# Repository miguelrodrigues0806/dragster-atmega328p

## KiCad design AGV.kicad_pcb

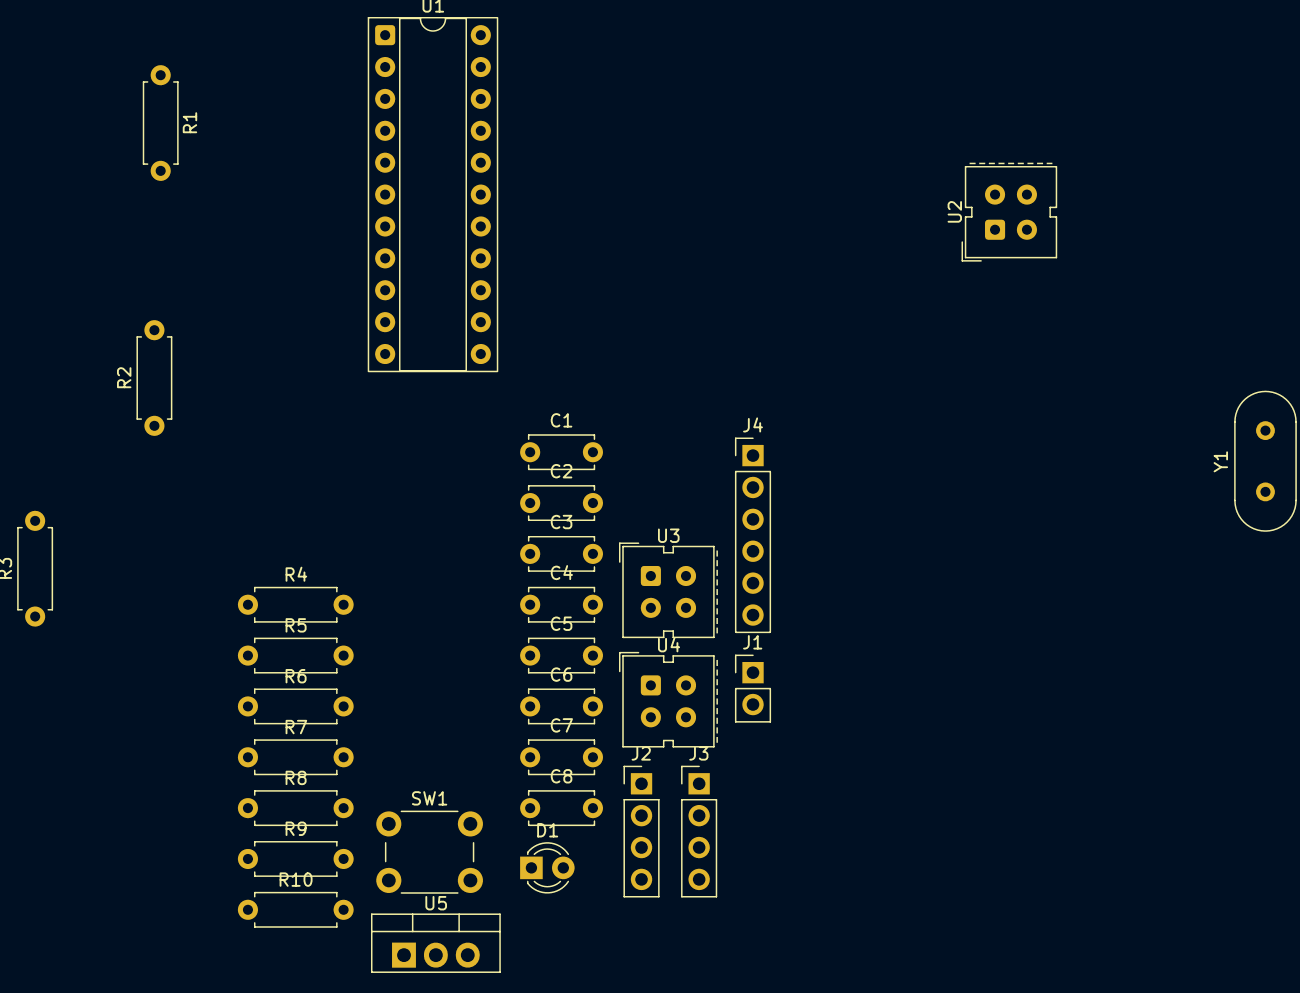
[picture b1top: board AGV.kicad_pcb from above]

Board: 2 copper layers, 30 parts (0 on the bottom side), 26 nets, no tracks yet.

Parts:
C1, C2, C3, C7: 100nF; C_Disc_D5.0mm_W2.5mm_P5.00mm
C4, C5: 22pF; C_Disc_D5.0mm_W2.5mm_P5.00mm
C6: 100n; C_Disc_D5.0mm_W2.5mm_P5.00mm
C8: 330nF; C_Disc_D5.0mm_W2.5mm_P5.00mm
D1: LED; LED_D3.0mm
J1: Conn_01x02_Pin; PinHeader_1x02_P2.54mm_Vertical
J2, J3: Conn_01x04_Pin; PinHeader_1x04_P2.54mm_Vertical
J4: Conn_01x06_Pin; PinHeader_1x06_P2.54mm_Vertical
R1, R3, R5, R7, R8: 10k; R_Axial_DIN0207_L6.3mm_D2.5mm_P7.62mm_Horizontal
R2, R4, R6: 220; R_Axial_DIN0207_L6.3mm_D2.5mm_P7.62mm_Horizontal
R9: 4.7k; R_Axial_DIN0207_L6.3mm_D2.5mm_P7.62mm_Horizontal
R10: 330; R_Axial_DIN0207_L6.3mm_D2.5mm_P7.62mm_Horizontal
SW1: SW_Push; SW_PUSH_6mm
U1: ATmega328P-P; DIP-22_W7.62mm_Socket
U2, U3, U4: CNY70; Vishay_CNY70
U5: LM7805_TO220; TO-220-3_Vertical
Y1: 12MHz; Crystal_HC49-U_Vertical

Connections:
+5V: C2.2, C3.2, C7.1, J2.1, J3.1, R1.2, R2.1, R4.1, R6.1, U1.7 (VCC), U1.20 (AVCC), U2.3 (C), U3.3 (C), U4.3 (C), U5.3 (VO)
/BAT_SENSE: C6.1, R8.2, R9.1
/BT_RX: J2.4, U1.3 (PD1)
/BT_TX: J2.3, U1.2 (PD0)
/CNY_CENTER: R5.2, U3.4 (E)
/CNY_LEFT: R3.2, U2.4 (E)
/CNY_RIGHT: R7.2, U4.4 (E)
/MOT_IN1: J4.3, U1.14 (PB0)
/MOT_IN2: J4.4, U1.16 (PB2)
/MOT_IN3: J4.5, U1.18 (PB4)
/MOT_IN4: J4.6, U1.19 (PB5)
/PWM_ENA: J4.1, U1.11 (PD5)
/PWM_ENB: J4.2, U1.12 (PD6)
/SONAR_ECHO: J3.3, U1.4 (PD2)
/SONAR_TRIG: J3.2, U1.6 (PD4)
/V_BAT: C8.2, J1.1, R8.1, U5.1 (VI)
GND: C1.2, C2.1, C3.1, C4.2, C5.2, C6.2, C7.2, C8.1, D1.1 (K), J1.2, J2.2, J3.4, R3.1, R5.1, R7.1, R9.2, SW1.1, U1.8 (GND), U1.22 (GND), U2.2 (K), U3.2 (K), U4.2 (K), U5.2 (GND)
unnamed: D1.2 (A), R10.2
unnamed: C1.1, U1.21 (AREF)
unnamed: R10.1, U1.15 (PB1)
unnamed: C4.1, U1.9 (XTAL1/PB6), Y1.2
unnamed: C5.1, U1.10 (XTAL2/PB7), Y1.1
unnamed: R1.1, SW1.2, U1.1 (~RESET/PC6)
unnamed: R2.2, U2.1 (A)
unnamed: R4.2, U3.1 (A)
unnamed: R6.2, U4.1 (A)

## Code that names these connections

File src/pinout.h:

// config.h - Atribuição Oficial de Pinos ATmega328P
#ifndef CONFIG_H
#define CONFIG_H

// Comunicação Bluetooth (USART)
#define PIN_RX          0 // PD0
#define PIN_TX          1 // PD1

// Sensores de Obstáculos e Controlo
#define PIN_SONAR_ECHO  2 // PD2 (INT0)
#define PIN_BTN_START   3 // PD3 (INT1)
#define PIN_SONAR_TRIG  4 // PD4

// Motores - PWM (Timer 0)
#define PIN_PWM_ENA     5 // PD5 (OC0B)
#define PIN_PWM_ENB     6 // PD6 (OC0A)

// Motores - Direção (L298N)
#define PIN_MOT_IN1     0 // PB0
#define PIN_MOT_IN2     2 // PB2
#define PIN_MOT_IN3     4 // PB4
#define PIN_MOT_IN4     5 // PB5

// Sinalização LABSI
#define PIN_LED_1HZ     1 // PB1

// Sensores Analógicos (ADC)
#define ADC_CNY_LEFT    0 // PC0 (A0)
#define ADC_CNY_CENTER  1 // PC1 (A1)
#define ADC_CNY_RIGHT   2 // PC2 (A2)
#define ADC_BATTERY     5 // PC5 (A5)

#endif
